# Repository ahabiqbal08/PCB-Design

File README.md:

# ELEC2133 Signal Generator

A two-layer through-hole PCB that generates a **square wave**, converts it to a **triangle wave**, and then to an approximately **sine wave**, using four LM741 op-amps. Designed in KiCad 10.

**Author:** Ahab Iqbal
**Date:** July 2026

---

## How it works

The circuit is a chain of four op-amp stages. Each stage feeds the next.

```
 Relaxation      Lossy            Lossy            Inverting
 oscillator  ->  integrator   ->  integrator   ->  amplifier
   (U1)            (U2)             (U3)             (U4)
  square         triangle          ~sine         output stage
```

| Stage | IC | Function | Key components |
|-------|----|----------|----------------|
| 1 | U1 | **Square wave** – astable (relaxation) oscillator with positive feedback | R1 = 100k, C1 = 10 nF (timing); R2 = 100k, R3 = 27k (threshold divider) |
| 2 | U2 | **Triangle wave** – integrates the square wave | R4 = 10k input; C2 = 100 nF with R5 = 100k in parallel as feedback; R6 = 10k bias resistor |
| 3 | U3 | **Sine-like wave** – integrates and smooths the triangle | R7 = 10k input; C3 = 10 nF with R9 = 100k in parallel as feedback; R8 = 10k bias resistor |
| 4 | U4 | **Output amplifier** – inverting gain stage | R10 = 10k input, R12 = 27k feedback (gain ≈ −2.7); R11 = 10k bias resistor |

Each op-amp has a trimmer (RV1–RV4) across its offset-null pins (1 and 5), with the wiper tied to −15 V. This is the standard LM741 offset adjustment.

### Expected frequency

From the component values, the oscillator in stage 1 should run at roughly **1.16 kHz**:

```
beta = R3 / (R2 + R3) = 27k / 127k ≈ 0.213
f    = 1 / (2 · R1 · C1 · ln((1 + beta) / (1 − beta))) ≈ 1.16 kHz
```

This is a theoretical estimate that assumes an ideal op-amp and symmetric output saturation. Measured values will differ because of component tolerances and the 741's slew rate.

---

## Power

The board needs a **dual supply of ±15 V**.

| Connector | Net | Notes |
|-----------|-----|-------|
| J1 | +15 V | 2-pin header (both pins tied together) |
| J2 | GND | 2-pin header (both pins tied together) |
| J3 | −15 V | 2-pin header (both pins tied together) |

C4 (100 nF, +15 V to GND) and C5 (100 nF, GND to −15 V) provide supply decoupling.

---

## Taking measurements

| Waveform | Probe point |
|----------|-------------|
| Square | U1 pin 6 |
| Triangle | U2 pin 6 |
| Sine-like | U3 pin 6 |
| Final output (inverted, amplified sine) | U4 pin 6 |

Use any GND pin on J2 as the reference.

---

## Bill of materials

| Ref | Value | Qty | Footprint |
|-----|-------|-----|-----------|
| U1–U4 | LM741 | 4 | DIP-8 (7.62 mm) |
| R1, R2, R5, R9 | 100k | 4 | Axial DIN0207, 10.16 mm pitch |
| R4, R6, R7, R8, R10, R11 | 10k | 6 | Axial DIN0207, 10.16 mm pitch |
| R3, R12 | 27k | 2 | Axial DIN0207, 10.16 mm pitch |
| C1, C3 | 10 nF (0.01 µF) | 2 | Disc, 5.0 mm dia, 2.5 mm pitch |
| C2 | 100 nF (0.1 µF) | 1 | Disc, 5.0 mm dia, 2.5 mm pitch |
| C4, C5 | 100 nF | 2 | Disc, 5.0 mm dia, 2.5 mm pitch |
| RV1–RV4 | Potentiometer (value not specified in schematic) | 4 | Bourns 3296W vertical |
| J1–J3 | 1×2 pin header | 3 | 2.54 mm, vertical SMD |

---

## Repository contents

```
elec2133_bonus/
├── elec2133_bonus.kicad_pro      KiCad project file
├── elec2133_bonus.kicad_sch      Schematic
├── elec2133_bonus.kicad_pcb      PCB layout
├── elec2133_bonus.kicad_prl      Local project settings
├── ERC.rpt                       Electrical rules check report (0 errors, 0 warnings)
├── elec2133_bonus-*.gbr          Gerber files (copper, mask, paste, silkscreen, edge cuts)
├── elec2133_bonus-PTH.drl        Plated drill file
├── elec2133_bonus-NPTH.drl       Non-plated drill file
├── elec2133_bonus-job.gbrjob     Gerber job file
└── .history/                     KiCad local history (automatic snapshots)
```

## Board specifications

| Property | Value |
|----------|-------|
| Layers | 2 (F.Cu / B.Cu) |
| Thickness | 1.6 mm |
| Size | ≈ 85.9 × 59.6 mm |
| Min track width / clearance | 0.2 mm / 0.2 mm |

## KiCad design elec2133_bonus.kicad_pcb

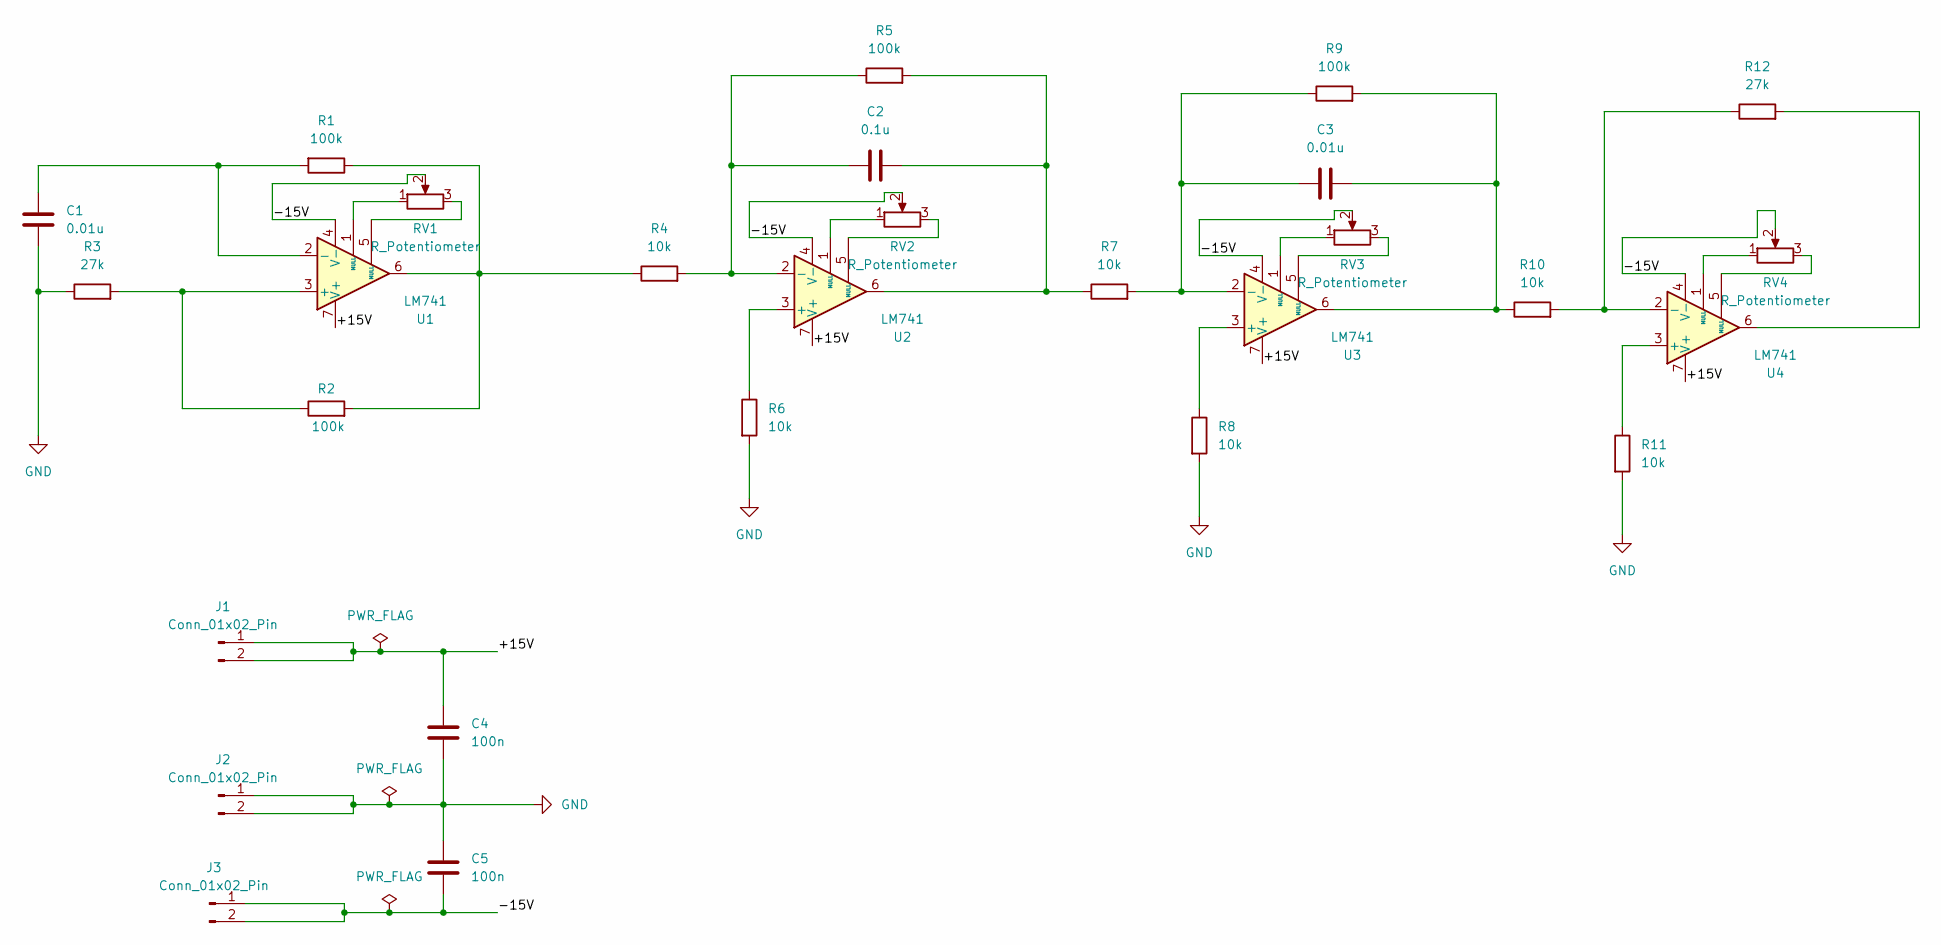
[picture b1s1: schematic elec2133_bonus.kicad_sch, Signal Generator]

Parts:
C1, C3: 0.01u; C_Disc_D5.0mm_W2.5mm_P2.50mm
C2: 0.1u; C_Disc_D5.0mm_W2.5mm_P2.50mm
C4, C5: 100n; C_Disc_D5.0mm_W2.5mm_P2.50mm
J1, J2, J3: Conn_01x02_Pin; PinHeader_1x02_P2.54mm_Vertical_SMD_Pin1Right
R1, R2, R5, R9: 100k; R_Axial_DIN0207_L6.3mm_D2.5mm_P10.16mm_Horizontal
R3, R12: 27k; R_Axial_DIN0207_L6.3mm_D2.5mm_P10.16mm_Horizontal
R4, R6, R7, R8, R10, R11: 10k; R_Axial_DIN0207_L6.3mm_D2.5mm_P10.16mm_Horizontal
RV1, RV2, RV3, RV4: R_Potentiometer; Potentiometer_Bourns_3296W_Vertical
U1, U2, U3, U4: LM741; DIP-8_W7.62mm

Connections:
/+15V: C4.1, J1.1, J1.2, U1.7 (V+), U2.7 (V+), U3.7 (V+), U4.7 (V+)
/-15V: C5.2, J3.1, J3.2, RV1.2, RV2.2, RV3.2, RV4.2, U1.4 (V-), U2.4 (V-), U3.4 (V-), U4.4 (V-)
GND: C1.2, C4.2, C5.1, J2.1, J2.2, R3.1, R6.2, R8.2, R11.2
unnamed: C2.2, R5.2, R7.1, U2.6
unnamed: C3.2, R9.2, R10.1, U3.6
unnamed: R1.1, R2.2, R4.1, U1.6
unnamed: R12.2, U4.6
unnamed: RV1.1, U1.1 (NULL)
unnamed: RV1.3, U1.5 (NULL)
unnamed: RV2.1, U2.1 (NULL)
unnamed: RV2.3, U2.5 (NULL)
unnamed: RV3.1, U3.1 (NULL)
unnamed: RV3.3, U3.5 (NULL)
unnamed: RV4.1, U4.1 (NULL)
unnamed: RV4.3, U4.5 (NULL)
unnamed: R2.1, R3.2, U1.3 (+)
unnamed: C1.1, R1.2, U1.2 (-)
unnamed: R6.1, U2.3 (+)
unnamed: C2.1, R4.2, R5.1, U2.2 (-)
unnamed: R8.1, U3.3 (+)
unnamed: C3.1, R7.2, R9.1, U3.2 (-)
unnamed: R11.1, U4.3 (+)
unnamed: R10.2, R12.1, U4.2 (-)

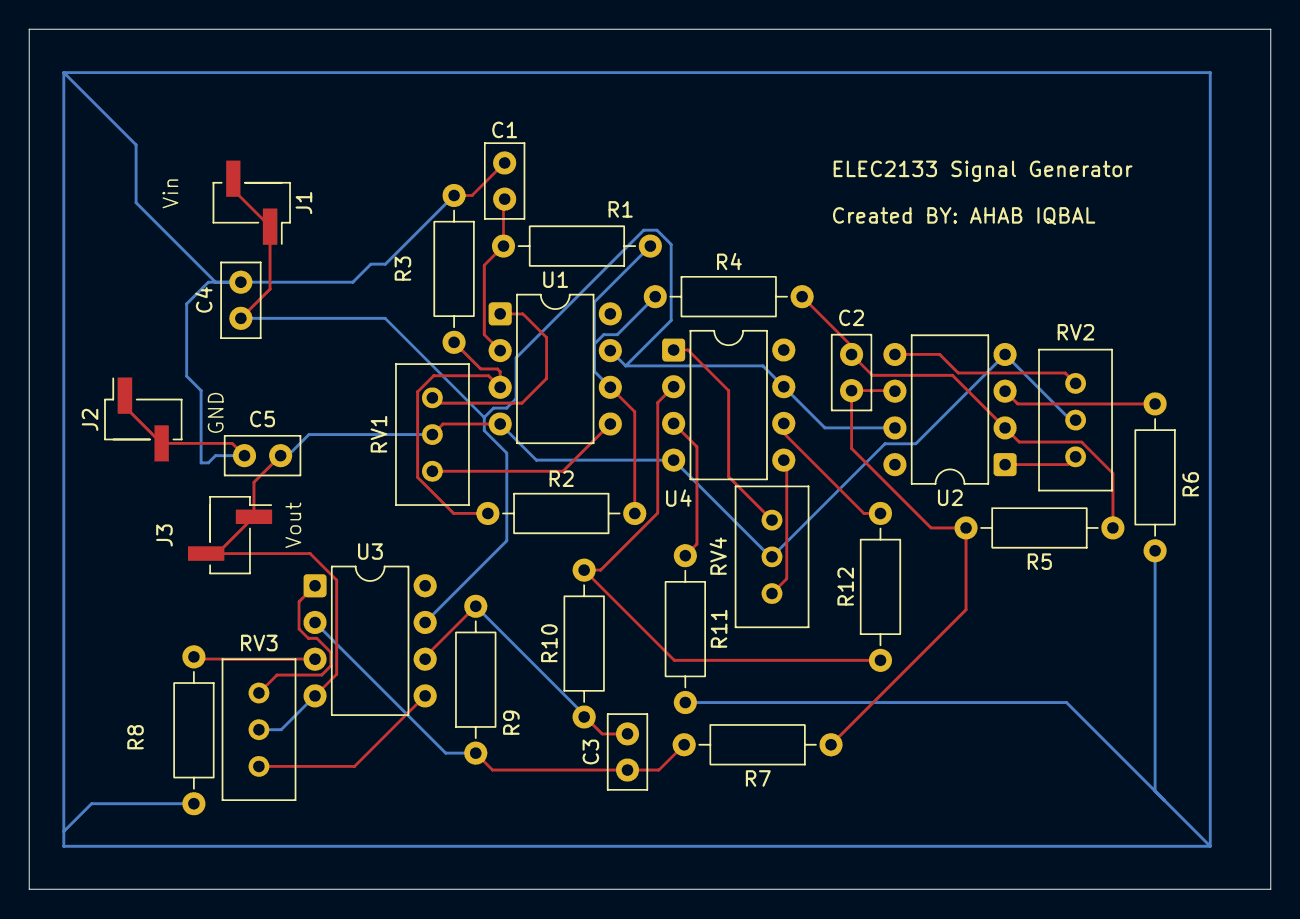
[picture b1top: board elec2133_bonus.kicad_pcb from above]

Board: 2 copper layers, 85.9 x 59.5 mm, 28 parts (0 on the bottom side), 23 nets.
